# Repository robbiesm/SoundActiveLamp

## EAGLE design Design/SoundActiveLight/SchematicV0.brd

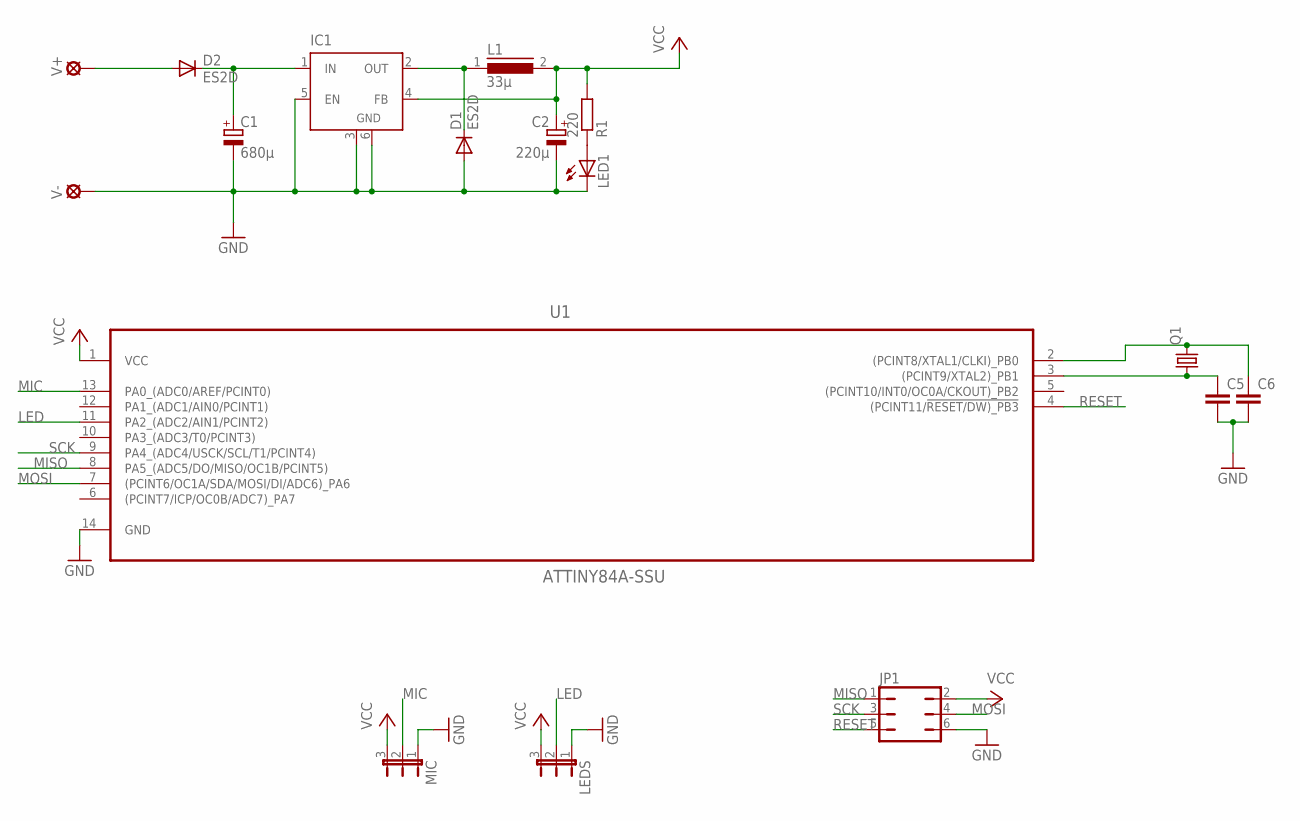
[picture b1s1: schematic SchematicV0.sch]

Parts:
C1: 680µ; 140CLH-1010
C2: 220µ; 140CLH-1010
C5, C6: CC1005; C1005
D1, D2: ES2D; SMB
IC1: LM2596S; TO263-5
JP1: JP3Q
L1: 33µ; DR125
LED1: LED_E; LED_1206
LEDS: JP2E; JP2
MIC: JP2E; JP2
Q1: CRYSTALHC49S; HC49/S
R1: 220; R0805
U1: ATTINY84A-SSU; SOIC127P600X175-14N
V+: SE14
V-: SE14

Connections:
GND: C1.-, C2.-, C5.2, C6.2, D1.A, IC1.3 (GND), IC1.5 (EN), IC1.6 (GND), JP1.6, LED1.C, LEDS.1, MIC.1, U1.14 (GND), V-.MP
LED: LEDS.2, U1.11 (PA2_(ADC2/AIN1/PCINT2))
MIC: MIC.2, U1.13 (PA0_(ADC0/AREF/PCINT0))
MISO: JP1.1, U1.8 (PA5_(ADC5/DO/MISO/OC1B/PCINT5))
MOSI: JP1.4, U1.7 ((PCINT6/OC1A/SDA/MOSI/DI/ADC6)_PA6)
unnamed: C1.+, D2.C, IC1.1 (IN)
unnamed: D2.A, V+.MP
unnamed: C5.1, Q1.1, U1.3 ((PCINT9/XTAL2)_PB1)
unnamed: C6.1, Q1.2, U1.2 ((PCINT8/XTAL1/CLKI)_PB0)
unnamed: D1.C, IC1.2 (OUT), L1.1
unnamed: LED1.A, R1.1
RESET: JP1.5, U1.4 ((PCINT11/!RESET/DW)_PB3)
SCK: JP1.3, U1.9 (PA4_(ADC4/USCK/SCL/T1/PCINT4))
VCC: C2.+, IC1.4 (FB), JP1.2, L1.2, LEDS.3, MIC.3, R1.2, U1.1 (VCC)

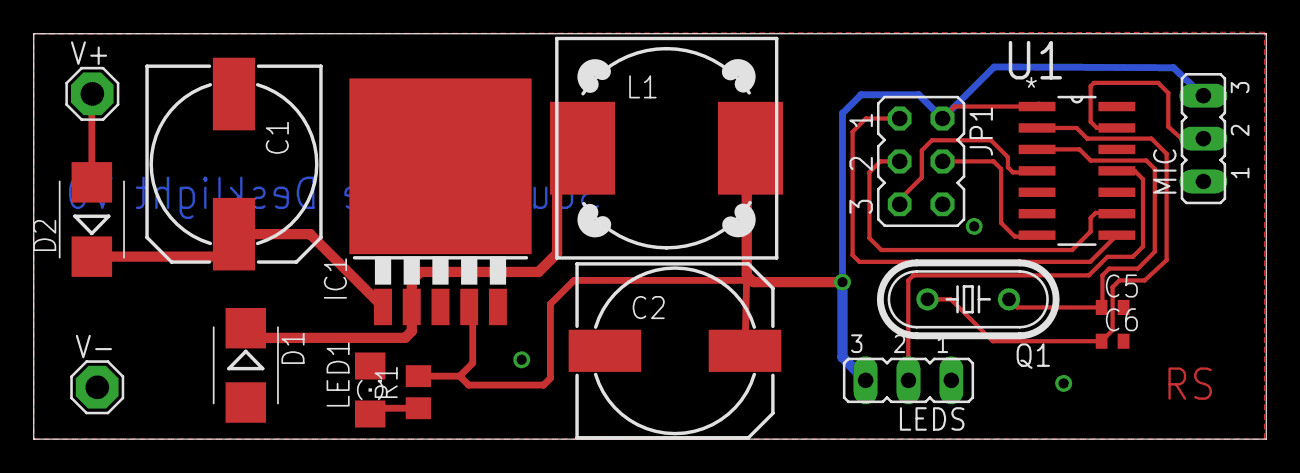
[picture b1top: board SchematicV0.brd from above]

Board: 2 copper layers, 73.0 x 24.0 mm, 17 parts (0 on the bottom side), 14 nets.

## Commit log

2018-03-14 :confetti_ball: Added .gitattributes & .gitignore files
2018-03-14 Initial upload
    start code for fastLED library
2018-04-03 changes
    Changed some functions for compatibility with ATtiny84A
2018-11-20 laptop upload
